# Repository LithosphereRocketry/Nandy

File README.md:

# NANDy
Nandy (capitalization variable) is an 8-bit RISC computer architecture built for implementation using simple 74xx-series discrete NAND gates. It was inspired by the theorem shown in most digital logic classes that any piece of combinational logic may be recreated as a network of NAND gates.

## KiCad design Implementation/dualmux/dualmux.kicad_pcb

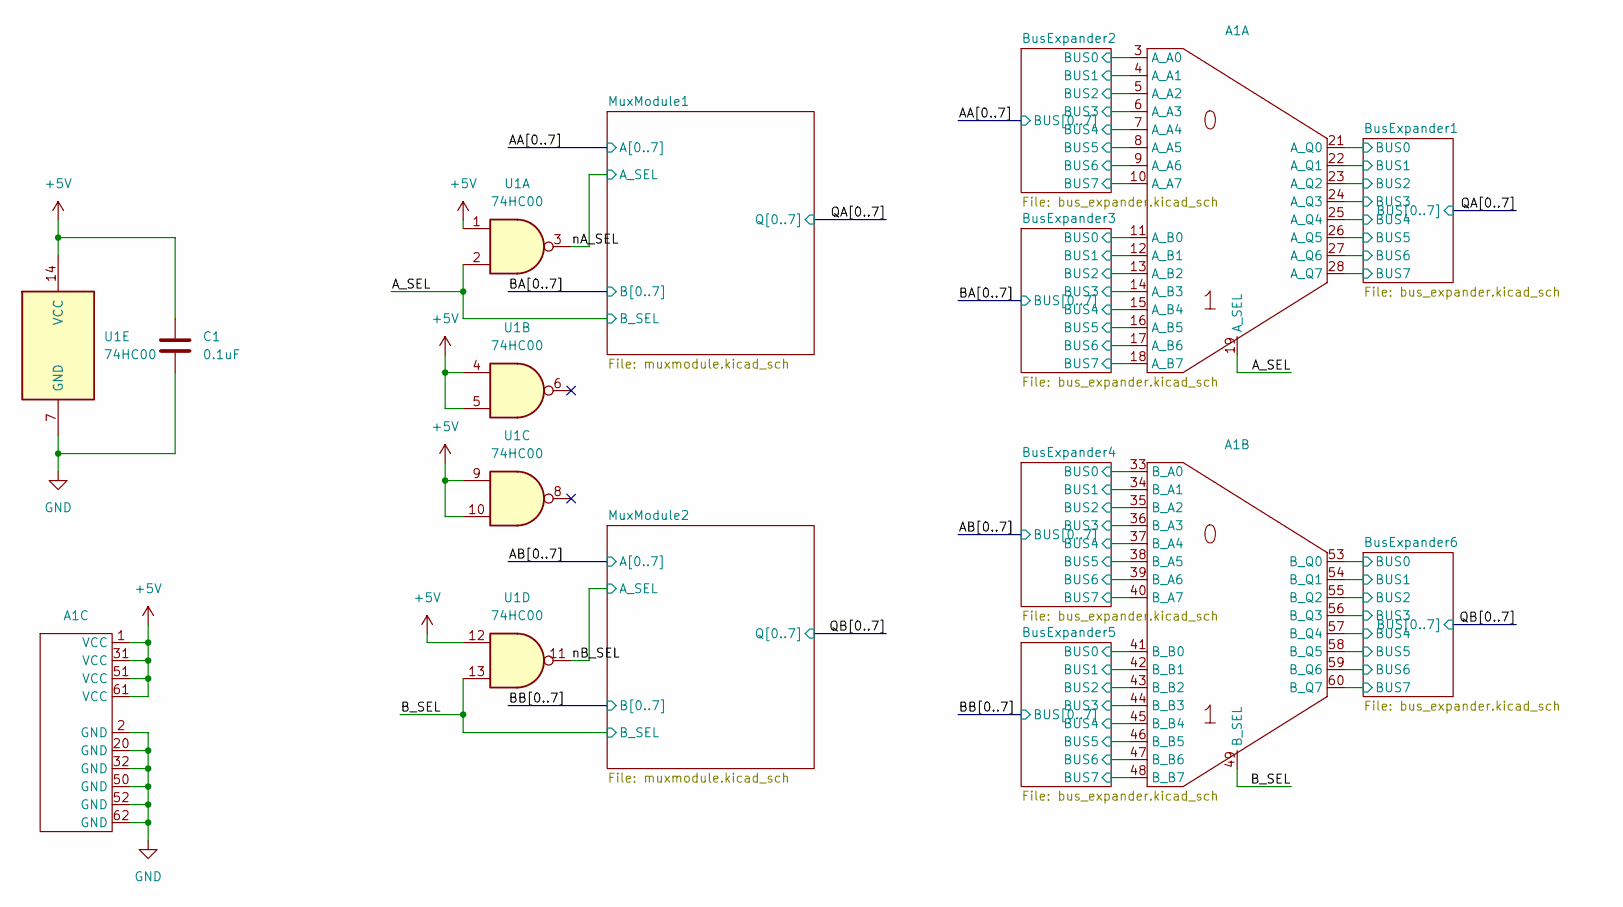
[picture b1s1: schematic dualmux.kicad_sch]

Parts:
A1: EDAC_395-DualMux-CardEdge
C1: 0.1uF; C_Disc_D4.3mm_W1.9mm_P5.00mm
U1: 74HC00; DIP-14_W7.62mm_Socket

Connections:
+5V: A1.1 (VCC), A1.31 (VCC), A1.51 (VCC), A1.61 (VCC), C1.1, U1.1, U1.4, U1.5, U1.9, U1.10, U1.12, U1.14 (VCC); also elsewhere on the board
/AA0: A1.3 (A_A0); also elsewhere on the board
/AA1: A1.4 (A_A1); also elsewhere on the board
/AA2: A1.5 (A_A2); also elsewhere on the board
/AA3: A1.6 (A_A3); also elsewhere on the board
/AA4: A1.7 (A_A4); also elsewhere on the board
/AA5: A1.8 (A_A5); also elsewhere on the board
/AA6: A1.9 (A_A6); also elsewhere on the board
/AA7: A1.10 (A_A7); also elsewhere on the board
/AB0: A1.33 (B_A0); also elsewhere on the board
/AB1: A1.34 (B_A1); also elsewhere on the board
/AB2: A1.35 (B_A2); also elsewhere on the board
/AB3: A1.36 (B_A3); also elsewhere on the board
/AB4: A1.37 (B_A4); also elsewhere on the board
/AB5: A1.38 (B_A5); also elsewhere on the board
/AB6: A1.39 (B_A6); also elsewhere on the board
/AB7: A1.40 (B_A7); also elsewhere on the board
/A_SEL: A1.19 (A_SEL), U1.2; also elsewhere on the board
/BA0: A1.11 (A_B0); also elsewhere on the board
/BA1: A1.12 (A_B1); also elsewhere on the board
/BA2: A1.13 (A_B2); also elsewhere on the board
/BA3: A1.14 (A_B3); also elsewhere on the board
/BA4: A1.15 (A_B4); also elsewhere on the board
/BA5: A1.16 (A_B5); also elsewhere on the board
/BA6: A1.17 (A_B6); also elsewhere on the board
/BA7: A1.18 (A_B7); also elsewhere on the board
/BB0: A1.41 (B_B0); also elsewhere on the board
/BB1: A1.42 (B_B1); also elsewhere on the board
/BB2: A1.43 (B_B2); also elsewhere on the board
/BB3: A1.44 (B_B3); also elsewhere on the board
/BB4: A1.45 (B_B4); also elsewhere on the board
/BB5: A1.46 (B_B5); also elsewhere on the board
/BB6: A1.47 (B_B6); also elsewhere on the board
/BB7: A1.48 (B_B7); also elsewhere on the board
/B_SEL: A1.49 (B_SEL), U1.13; also elsewhere on the board
/QA0: A1.21 (A_Q0); also elsewhere on the board
/QA1: A1.22 (A_Q1); also elsewhere on the board
/QA2: A1.23 (A_Q2); also elsewhere on the board
/QA3: A1.24 (A_Q3); also elsewhere on the board
/QA4: A1.25 (A_Q4); also elsewhere on the board
/QA5: A1.26 (A_Q5); also elsewhere on the board
/QA6: A1.27 (A_Q6); also elsewhere on the board
/QA7: A1.28 (A_Q7); also elsewhere on the board
/QB0: A1.53 (B_Q0); also elsewhere on the board
/QB1: A1.54 (B_Q1); also elsewhere on the board
/QB2: A1.55 (B_Q2); also elsewhere on the board
/QB3: A1.56 (B_Q3); also elsewhere on the board
/QB4: A1.57 (B_Q4); also elsewhere on the board
/QB5: A1.58 (B_Q5); also elsewhere on the board
/QB6: A1.59 (B_Q6); also elsewhere on the board
/QB7: A1.60 (B_Q7); also elsewhere on the board
/nA_SEL: U1.3; also elsewhere on the board
/nB_SEL: U1.11; also elsewhere on the board
GND: A1.2 (GND), A1.20 (GND), A1.32 (GND), A1.50 (GND), A1.52 (GND), A1.62 (GND), C1.2, U1.7 (GND); also elsewhere on the board

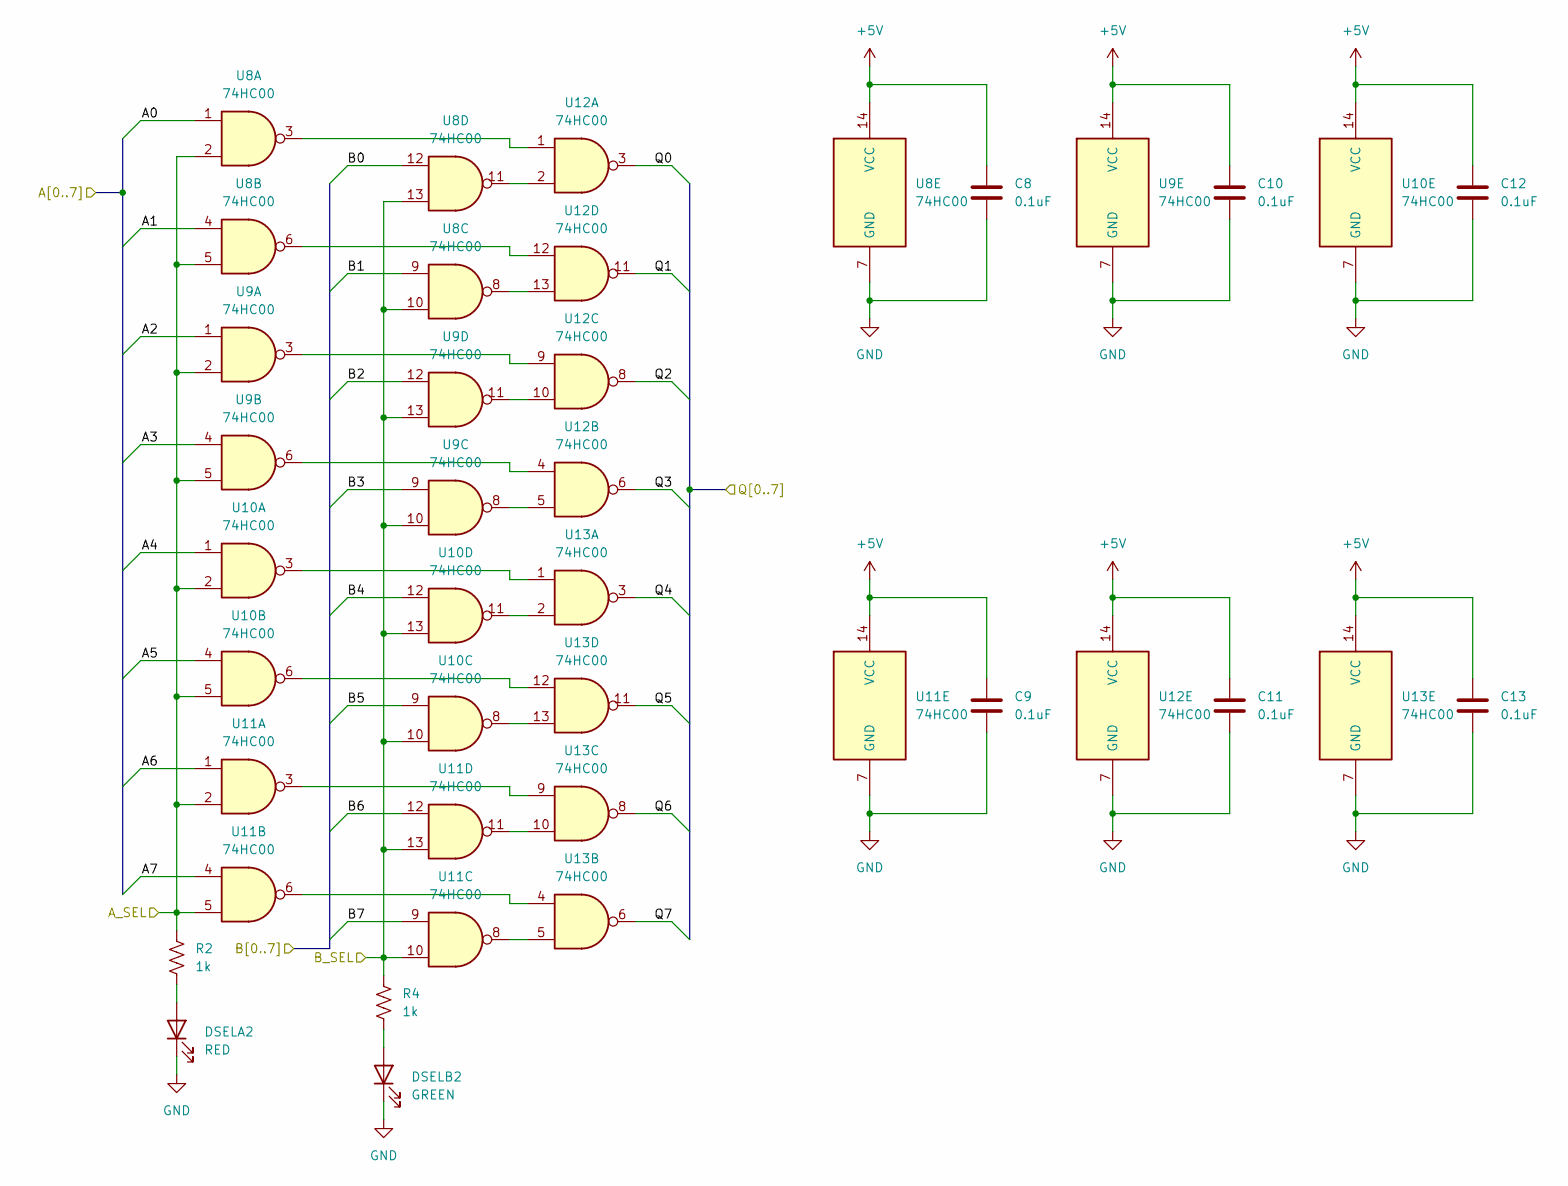
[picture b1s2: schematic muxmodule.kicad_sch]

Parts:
C8, C9, C10, C11, C12, C13: 0.1uF; C_Disc_D4.3mm_W1.9mm_P5.00mm
DSELA2: RED; LED_D5.0mm
DSELB2: GREEN; LED_D5.0mm
R2, R4: 1k; R_Axial_DIN0207_L6.3mm_D2.5mm_P10.16mm_Horizontal
U8, U9, U10, U11, U12, U13: 74HC00; DIP-14_W7.62mm_Socket

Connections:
+5V: C8.1, C9.1, C10.1, C11.1, C12.1, C13.1, U8.14 (VCC), U9.14 (VCC), U10.14 (VCC), U11.14 (VCC), U12.14 (VCC), U13.14 (VCC); also elsewhere on the board
/AB0: U8.1; also elsewhere on the board
/AB1: U8.4; also elsewhere on the board
/AB2: U9.1; also elsewhere on the board
/AB3: U9.4; also elsewhere on the board
/AB4: U10.1; also elsewhere on the board
/AB5: U10.4; also elsewhere on the board
/AB6: U11.1; also elsewhere on the board
/AB7: U11.4; also elsewhere on the board
/BB0: U8.12; also elsewhere on the board
/BB1: U8.9; also elsewhere on the board
/BB2: U9.12; also elsewhere on the board
/BB3: U9.9; also elsewhere on the board
/BB4: U10.12; also elsewhere on the board
/BB5: U10.9; also elsewhere on the board
/BB6: U11.12; also elsewhere on the board
/BB7: U11.9; also elsewhere on the board
/B_SEL: R4.1, U8.10, U8.13, U9.10, U9.13, U10.10, U10.13, U11.10, U11.13; also elsewhere on the board
/QB0: U12.3; also elsewhere on the board
/QB1: U12.11; also elsewhere on the board
/QB2: U12.8; also elsewhere on the board
/QB3: U12.6; also elsewhere on the board
/QB4: U13.3; also elsewhere on the board
/QB5: U13.11; also elsewhere on the board
/QB6: U13.8; also elsewhere on the board
/QB7: U13.6; also elsewhere on the board
/nB_SEL: R2.1, U8.2, U8.5, U9.2, U9.5, U10.2, U10.5, U11.2, U11.5; also elsewhere on the board
GND: C8.2, C9.2, C10.2, C11.2, C12.2, C13.2, DSELA2.1 (K), DSELB2.1 (K), U8.7 (GND), U9.7 (GND), U10.7 (GND), U11.7 (GND), U12.7 (GND), U13.7 (GND); also elsewhere on the board
unnamed: DSELA2.2 (A), R2.2
unnamed: DSELB2.2 (A), R4.2
unnamed: U10.3, U13.1
unnamed: U10.6, U13.12
unnamed: U10.8, U13.13
unnamed: U10.11, U13.2
unnamed: U11.3, U13.9
unnamed: U11.6, U13.4
unnamed: U11.8, U13.5
unnamed: U11.11, U13.10
unnamed: U8.3, U12.1
unnamed: U8.11, U12.2
unnamed: U9.6, U12.4
unnamed: U9.8, U12.5
unnamed: U9.3, U12.9
unnamed: U9.11, U12.10
unnamed: U8.6, U12.12
unnamed: U8.8, U12.13

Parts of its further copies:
C2, C3, C4, C5, C6, C7: 0.1uF; C_Disc_D4.3mm_W1.9mm_P5.00mm
DSELA1: RED; LED_D5.0mm
DSELB1: GREEN; LED_D5.0mm
R1, R3: 1k; R_Axial_DIN0207_L6.3mm_D2.5mm_P10.16mm_Horizontal
U2, U3, U4, U5, U6, U7: 74HC00; DIP-14_W7.62mm_Socket

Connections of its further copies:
+5V: C2.1, C3.1, C4.1, C5.1, C6.1, C7.1, U2.14 (VCC), U3.14 (VCC), U4.14 (VCC), U5.14 (VCC), U6.14 (VCC), U7.14 (VCC); also elsewhere on the board
/AA0: U2.1; also elsewhere on the board
/AA1: U2.4; also elsewhere on the board
/AA2: U3.1; also elsewhere on the board
/AA3: U3.4; also elsewhere on the board
/AA4: U4.1; also elsewhere on the board
/AA5: U4.4; also elsewhere on the board
/AA6: U5.1; also elsewhere on the board
/AA7: U5.4; also elsewhere on the board
/A_SEL: R3.1, U2.10, U2.13, U3.10, U3.13, U4.10, U4.13, U5.10, U5.13; also elsewhere on the board
/BA0: U2.12; also elsewhere on the board
/BA1: U2.9; also elsewhere on the board
/BA2: U3.12; also elsewhere on the board
/BA3: U3.9; also elsewhere on the board
/BA4: U4.12; also elsewhere on the board
/BA5: U4.9; also elsewhere on the board
/BA6: U5.12; also elsewhere on the board
/BA7: U5.9; also elsewhere on the board
/QA0: U6.3; also elsewhere on the board
/QA1: U6.11; also elsewhere on the board
/QA2: U6.8; also elsewhere on the board
/QA3: U6.6; also elsewhere on the board
/QA4: U7.3; also elsewhere on the board
/QA5: U7.11; also elsewhere on the board
/QA6: U7.8; also elsewhere on the board
/QA7: U7.6; also elsewhere on the board
/nA_SEL: R1.1, U2.2, U2.5, U3.2, U3.5, U4.2, U4.5, U5.2, U5.5; also elsewhere on the board
GND: C2.2, C3.2, C4.2, C5.2, C6.2, C7.2, DSELA1.1 (K), DSELB1.1 (K), U2.7 (GND), U3.7 (GND), U4.7 (GND), U5.7 (GND), U6.7 (GND), U7.7 (GND); also elsewhere on the board
unnamed: DSELA1.2 (A), R1.2
unnamed: DSELB1.2 (A), R3.2
unnamed: U2.3, U6.1
unnamed: U2.6, U6.12
unnamed: U2.8, U6.13
unnamed: U2.11, U6.2
unnamed: U3.3, U6.9
unnamed: U3.6, U6.4
unnamed: U3.8, U6.5
unnamed: U3.11, U6.10
unnamed: U4.3, U7.1
unnamed: U4.6, U7.12
unnamed: U4.8, U7.13
unnamed: U4.11, U7.2
unnamed: U5.3, U7.9
unnamed: U5.6, U7.4
unnamed: U5.8, U7.5
unnamed: U5.11, U7.10

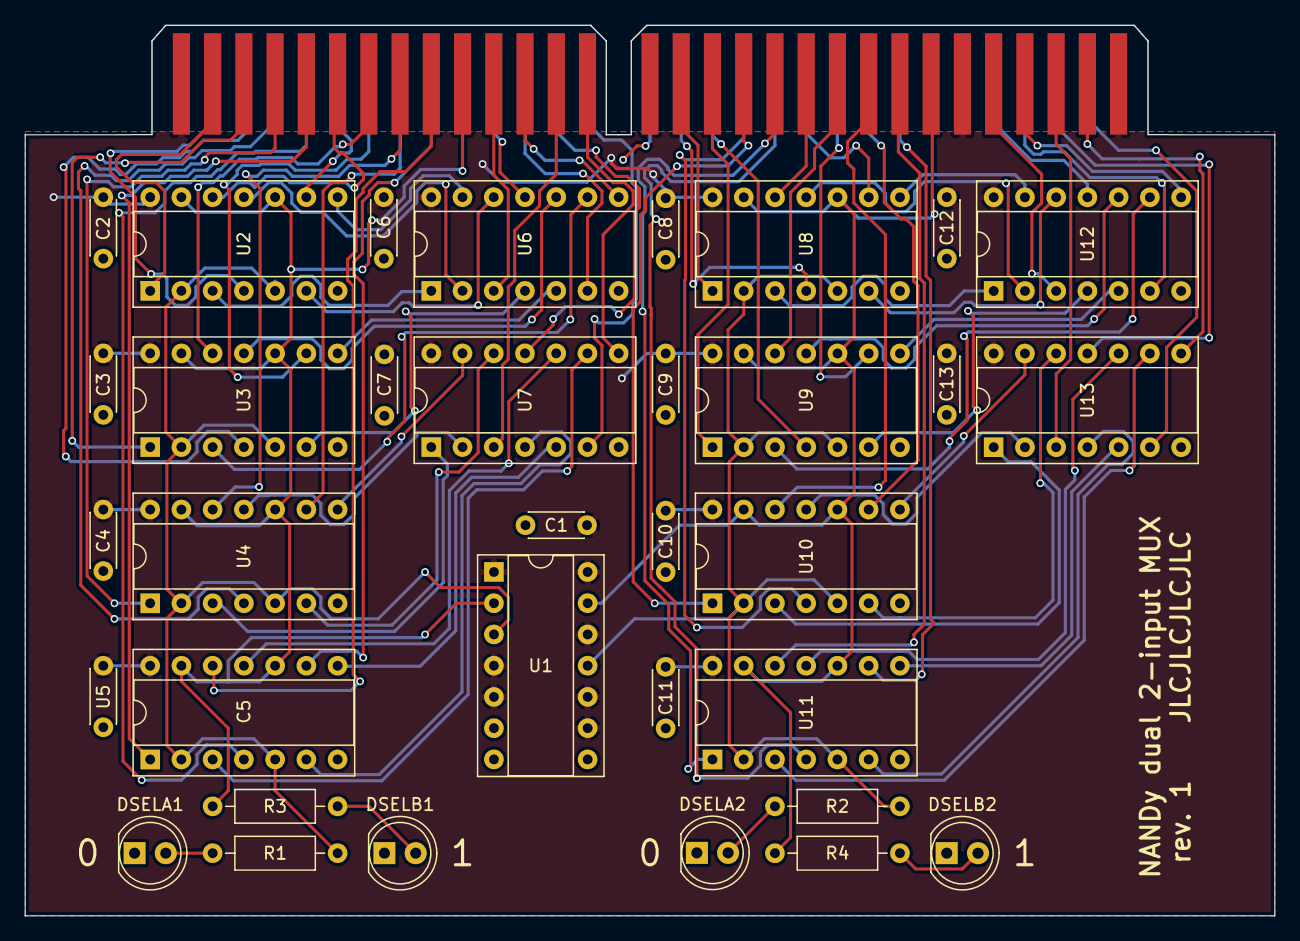
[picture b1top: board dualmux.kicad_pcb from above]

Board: 2 copper layers, 101.6 x 72.4 mm, 35 parts (1 on the bottom side), 90 nets.

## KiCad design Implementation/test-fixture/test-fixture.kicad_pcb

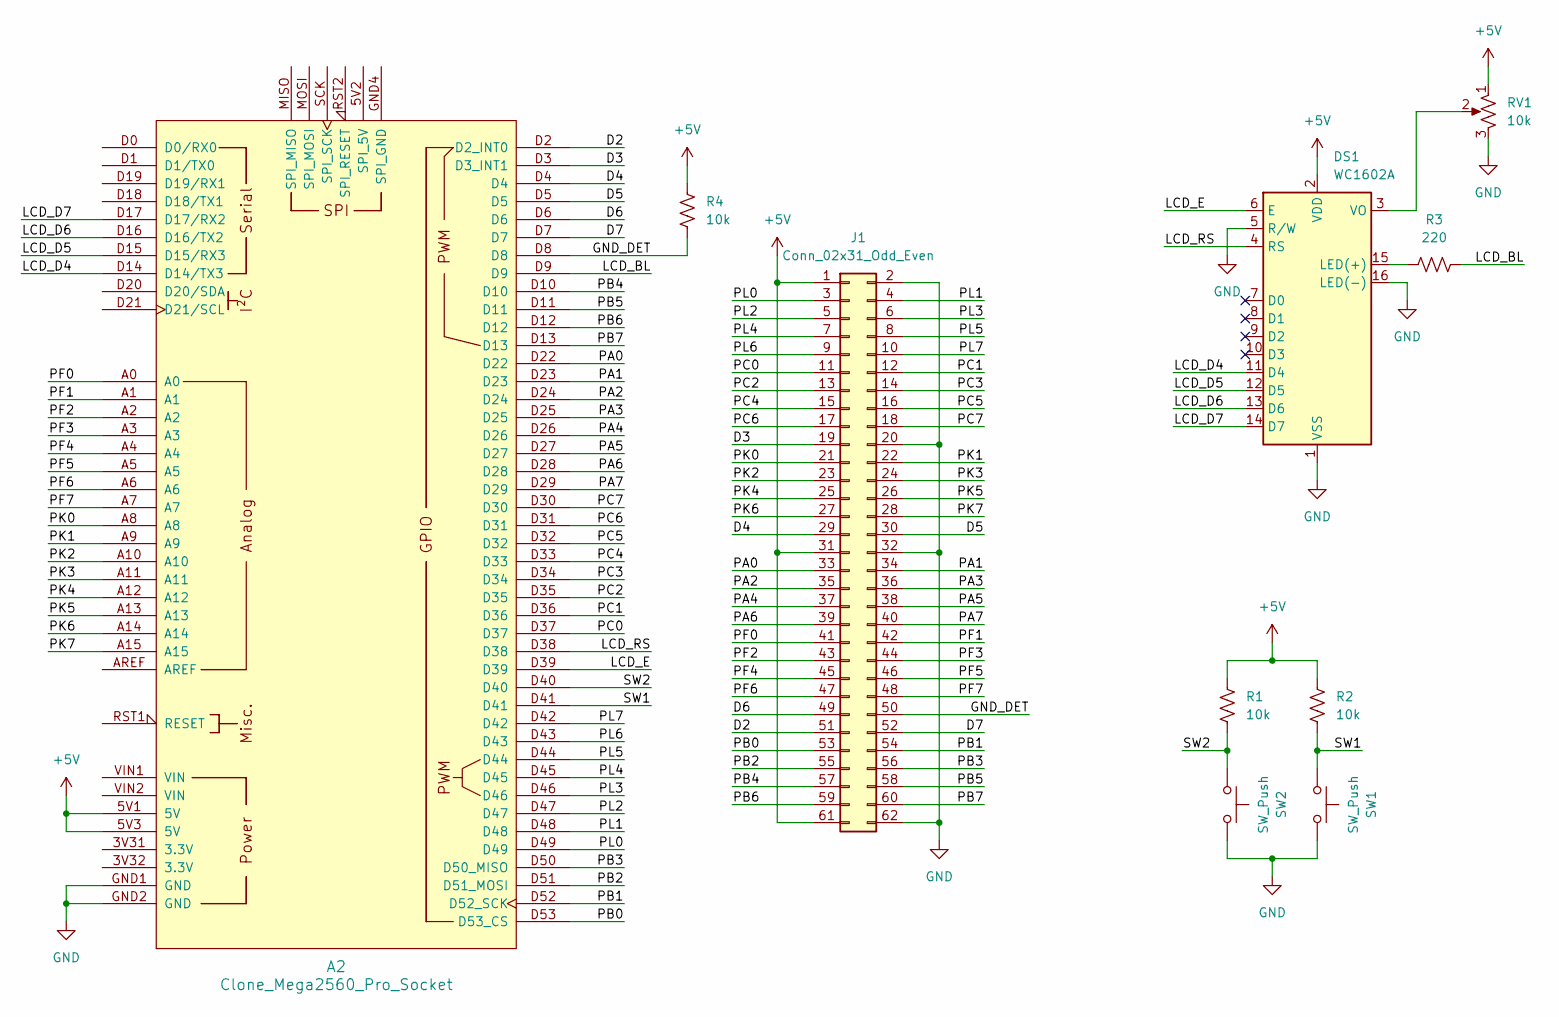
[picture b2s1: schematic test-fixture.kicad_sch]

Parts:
A2: Clone_Mega2560_Pro_Socket
DS1: WC1602A
J1: Conn_02x31_Odd_Even; EDAC_395-062-520-350
R1, R2, R4: 10k; R_Axial_DIN0207_L6.3mm_D2.5mm_P10.16mm_Horizontal
R3: 220; R_Axial_DIN0207_L6.3mm_D2.5mm_P10.16mm_Horizontal
RV1: 10k; Potentiometer_ACP_CA9-V10_Vertical
SW1, SW2: SW_Push; SW_PUSH_6mm

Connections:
+5V: A2.5V1 (5V), A2.5V3 (5V), DS1.2 (VDD), J1.1, J1.31, J1.61, R1.1, R2.1, R4.1, RV1.1
/D2: A2.D2 (D2_INT0), J1.51
/D3: A2.D3 (D3_INT1), J1.19
/D4: A2.D4, J1.29
/D5: A2.D5, J1.30
/D6: A2.D6, J1.49
/D7: A2.D7, J1.52
/GND_DET: A2.D8, J1.50, R4.2
/LCD_BL: A2.D9, R3.2
/LCD_D4: A2.D14 (D14/TX3), DS1.11 (D4)
/LCD_D5: A2.D15 (D15/RX3), DS1.12 (D5)
/LCD_D6: A2.D16 (D16/TX2), DS1.13 (D6)
/LCD_D7: A2.D17 (D17/RX2), DS1.14 (D7)
/LCD_E: A2.D39, DS1.6 (E)
/LCD_RS: A2.D38, DS1.4 (RS)
/PA0: A2.D22, J1.33
/PA1: A2.D23, J1.34
/PA2: A2.D24, J1.35
/PA3: A2.D25, J1.36
/PA4: A2.D26, J1.37
/PA5: A2.D27, J1.38
/PA6: A2.D28, J1.39
/PA7: A2.D29, J1.40
/PB0: A2.D53 (D53_CS), J1.53
/PB1: A2.D52 (D52_SCK), J1.54
/PB2: A2.D51 (D51_MOSI), J1.55
/PB3: A2.D50 (D50_MISO), J1.56
/PB4: A2.D10, J1.57
/PB5: A2.D11, J1.58
/PB6: A2.D12, J1.59
/PB7: A2.D13, J1.60
/PC0: A2.D37, J1.11
/PC1: A2.D36, J1.12
/PC2: A2.D35, J1.13
/PC3: A2.D34, J1.14
/PC4: A2.D33, J1.15
/PC5: A2.D32, J1.16
/PC6: A2.D31, J1.17
/PC7: A2.D30, J1.18
/PF0: A2.A0, J1.41
/PF1: A2.A1, J1.42
/PF2: A2.A2, J1.43
/PF3: A2.A3, J1.44
/PF4: A2.A4, J1.45
/PF5: A2.A5, J1.46
/PF6: A2.A6, J1.47
/PF7: A2.A7, J1.48
/PK0: A2.A8, J1.21
/PK1: A2.A9, J1.22
/PK2: A2.A10, J1.23
/PK3: A2.A11, J1.24
/PK4: A2.A12, J1.25
/PK5: A2.A13, J1.26
/PK6: A2.A14, J1.27
/PK7: A2.A15, J1.28
/PL0: A2.D49, J1.3
/PL1: A2.D48, J1.4
/PL2: A2.D47, J1.5
/PL3: A2.D46, J1.6
/PL4: A2.D45, J1.7
/PL5: A2.D44, J1.8
/PL6: A2.D43, J1.9
/PL7: A2.D42, J1.10
/SW1: A2.D41, R2.2, SW1.1
/SW2: A2.D40, R1.2, SW2.1
GND: A2.GND1 (GND), A2.GND2 (GND), DS1.1 (VSS), DS1.5 (R/W), DS1.16 (LED(-)), J1.2, J1.20, J1.32, J1.62, RV1.3, SW1.2, SW2.2
unnamed: DS1.15 (LED(+)), R3.1
unnamed: DS1.3 (VO), RV1.2

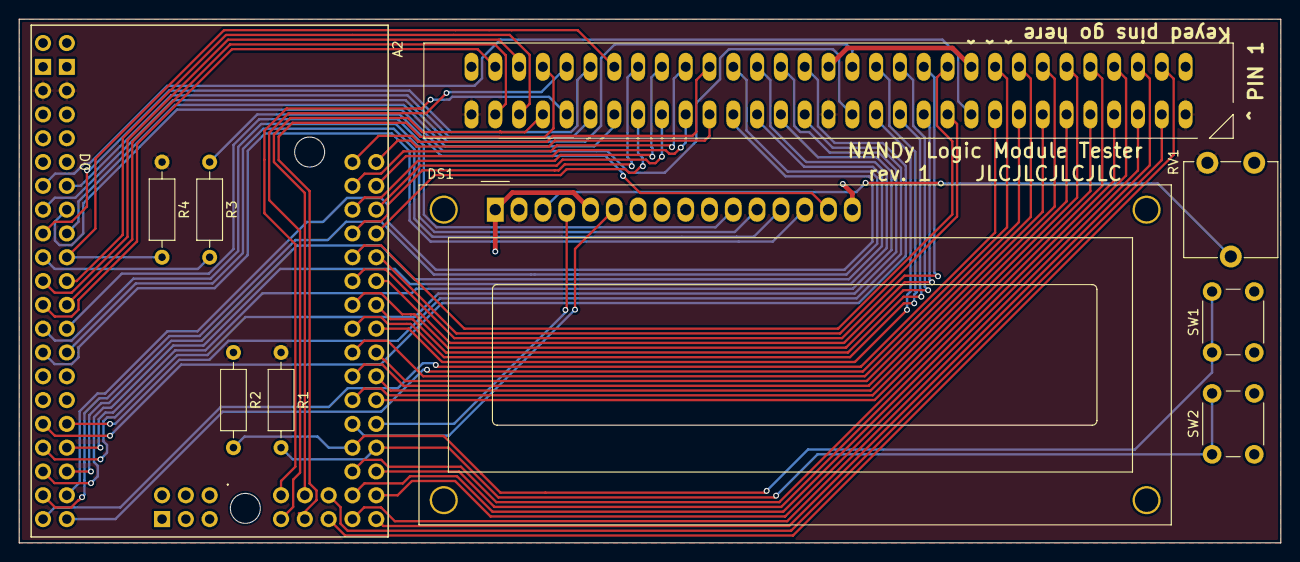
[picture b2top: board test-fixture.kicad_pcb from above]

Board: 2 copper layers, 134.6 x 55.9 mm, 10 parts (0 on the bottom side), 68 nets.

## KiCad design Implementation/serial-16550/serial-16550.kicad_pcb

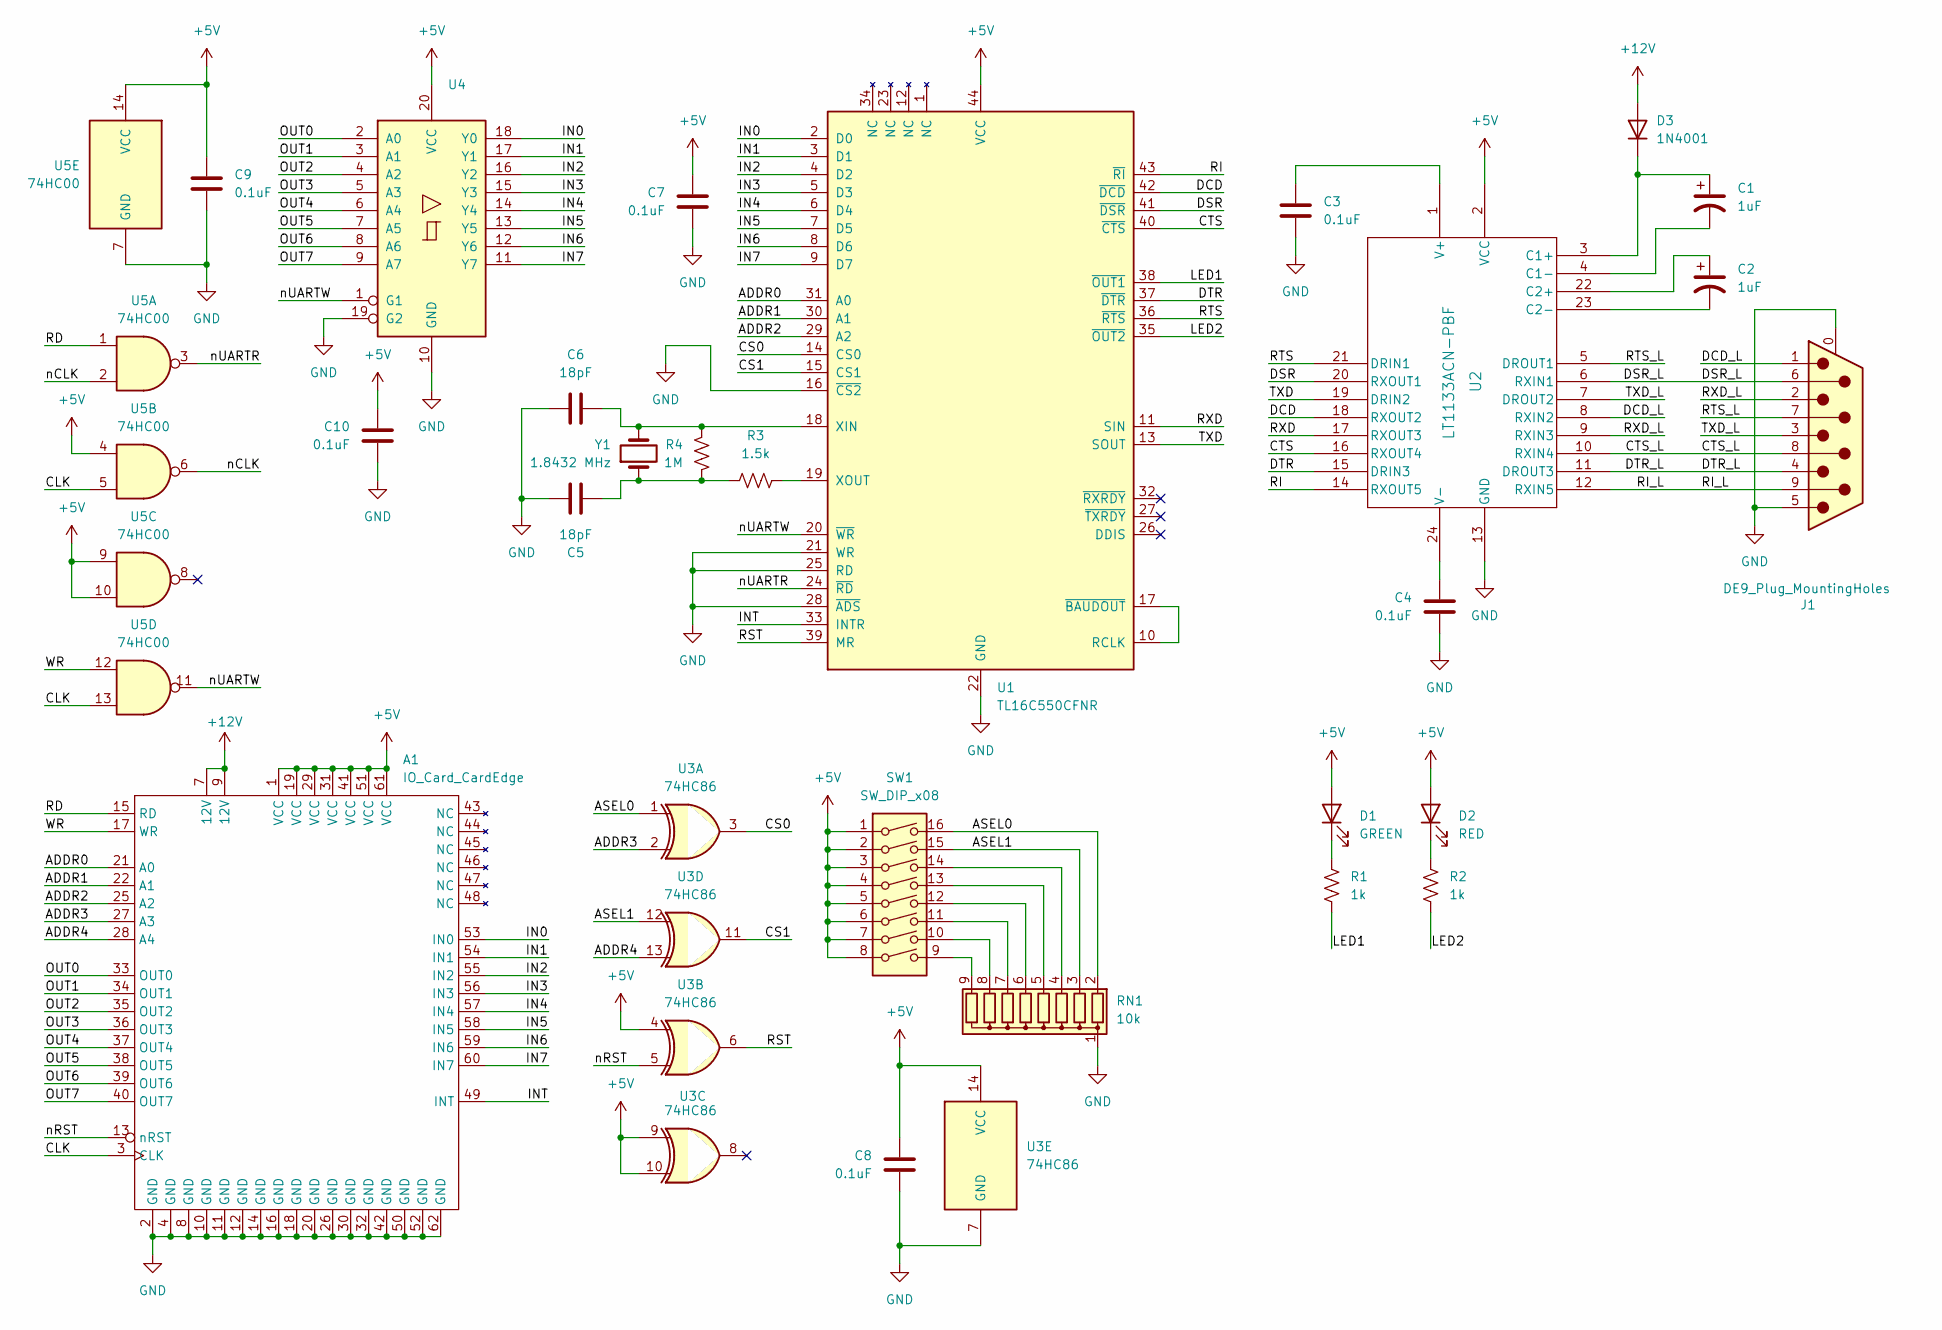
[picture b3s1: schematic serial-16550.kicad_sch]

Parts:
A1: IO_Card_CardEdge; EDAC_395-062-IOCard-CardEdge
C1, C2: 1uF; CP_Radial_Tantal_D7.0mm_P5.00mm
C3, C4, C7, C8, C9, C10: 0.1uF; C_Disc_D4.3mm_W1.9mm_P5.00mm
C5, C6: 18pF; C_Disc_D4.3mm_W1.9mm_P5.00mm
D1: GREEN; LED_D5.0mm
D2: RED; LED_D5.0mm
D3: 1N4001; D_DO-41_SOD81_P10.16mm_Horizontal
J1: DE9_Plug_MountingHoles; DSUB-9_Male_Horizontal_P2.77x2.84mm_EdgePinOffset7.70mm_Hou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
R1, R2: 1k; R_Axial_DIN0207_L6.3mm_D2.5mm_P10.16mm_Horizontal
R3: 1.5k; R_Axial_DIN0207_L6.3mm_D2.5mm_P10.16mm_Horizontal
R4: 1M; R_Axial_DIN0207_L6.3mm_D2.5mm_P10.16mm_Horizontal
RN1: 10k; R_Array_SIP9
SW1: SW_DIP_x08; SW_DIP_SPSTx08_Slide_6.7x21.88mm_W7.62mm_P2.54mm_LowProfile
U1: TL16C550CFNR; PLCC-44_THT-Socket
U2: LT1133ACN-PBF; DIP-24_W7.62mm
U3: 74HC86; DIP-14_W7.62mm_Socket
U4: 74AHC541; DIP-20_W7.62mm_Socket
U5: 74HC00; DIP-14_W7.62mm_Socket
Y1: 1.8432 MHz; Crystal_HC49-U_Vertical

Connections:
+5V: A1.1 (VCC), A1.19 (VCC), A1.29 (VCC), A1.31 (VCC), A1.41 (VCC), A1.51 (VCC), A1.61 (VCC), C7.1, C8.1, C9.1, C10.1, D1.2 (A), D2.2 (A), SW1.1, SW1.2, SW1.3, SW1.4, SW1.5, SW1.6, SW1.7, SW1.8, U1.44 (VCC), U2.2 (VCC), U3.4, U3.9, U3.10, U3.14 (VCC), U4.20 (VCC), U5.4, U5.9, U5.10, U5.14 (VCC)
+12V: A1.7 (12V), A1.9 (12V), D3.2 (A)
/ADDR0: A1.21 (A0), U1.31 (A0)
/ADDR1: A1.22 (A1), U1.30 (A1)
/ADDR2: A1.25 (A2), U1.29 (A2)
/ADDR3: A1.27 (A3), U3.2
/ADDR4: A1.28 (A4), U3.13
/ASEL0: RN1.2 (R1), SW1.16, U3.1
/ASEL1: RN1.3 (R2), SW1.15, U3.12
/CLK: A1.3 (CLK), U5.5, U5.13
/CS0: U1.14 (CS0), U3.3
/CS1: U1.15 (CS1), U3.11
/CTS: U1.40 (~CTS), U2.16 (RXOUT4)
/CTS_L: J1.8, U2.10 (RXIN4)
/DCD: U1.42 (~DCD), U2.18 (RXOUT2)
/DCD_L: J1.1, U2.8 (RXIN2)
/DSR: U1.41 (~DSR), U2.20 (RXOUT1)
/DSR_L: J1.6, U2.6 (RXIN1)
/DTR: U1.37 (~DTR), U2.15 (DRIN3)
/DTR_L: J1.4, U2.11 (DROUT3)
/IN0: A1.53 (IN0), U1.2 (D0), U4.18 (Y0)
/IN1: A1.54 (IN1), U1.3 (D1), U4.17 (Y1)
/IN2: A1.55 (IN2), U1.4 (D2), U4.16 (Y2)
/IN3: A1.56 (IN3), U1.5 (D3), U4.15 (Y3)
/IN4: A1.57 (IN4), U1.6 (D4), U4.14 (Y4)
/IN5: A1.58 (IN5), U1.7 (D5), U4.13 (Y5)
/IN6: A1.59 (IN6), U1.8 (D6), U4.12 (Y6)
/IN7: A1.60 (IN7), U1.9 (D7), U4.11 (Y7)
/INT: A1.49 (INT), U1.33 (INTR)
/LED1: R1.2, U1.38 (~OUT1)
/LED2: R2.2, U1.35 (~OUT2)
/OUT0: A1.33 (OUT0), U4.2 (A0)
/OUT1: A1.34 (OUT1), U4.3 (A1)
/OUT2: A1.35 (OUT2), U4.4 (A2)
/OUT3: A1.36 (OUT3), U4.5 (A3)
/OUT4: A1.37 (OUT4), U4.6 (A4)
/OUT5: A1.38 (OUT5), U4.7 (A5)
/OUT6: A1.39 (OUT6), U4.8 (A6)
/OUT7: A1.40 (OUT7), U4.9 (A7)
/RD: A1.15 (RD), U5.1
/RI: U1.43 (~RI), U2.14 (RXOUT5)
/RI_L: J1.9, U2.12 (RXIN5)
/RST: U1.39 (MR), U3.6
/RTS: U1.36 (~RTS), U2.21 (DRIN1)
/RTS_L: J1.7, U2.5 (DROUT1)
/RXD: U1.11 (SIN), U2.17 (RXOUT3)
/RXD_L: J1.2, U2.9 (RXIN3)
/TXD: U1.13 (SOUT), U2.19 (DRIN2)
/TXD_L: J1.3, U2.7 (DROUT2)
/WR: A1.17 (WR), U5.12
/nCLK: U5.2, U5.6
/nRST: A1.13 (nRST), U3.5
/nUARTR: U1.24 (~RD), U5.3
/nUARTW: U1.20 (~WR), U4.1 (G1), U5.11
GND: A1.2 (GND), A1.4 (GND), A1.8 (GND), A1.10 (GND), A1.11 (GND), A1.12 (GND), A1.14 (GND), A1.16 (GND), A1.18 (GND), A1.20 (GND), A1.26 (GND), A1.30 (GND), A1.32 (GND), A1.42 (GND), A1.50 (GND), A1.52 (GND), A1.62 (GND), C3.2, C4.2, C5.1, C6.2, C7.2, C8.2, C9.2, C10.2, J1.0 (PAD), J1.5, RN1.1 (common), U1.16 (~CS2), U1.21 (WR), U1.22 (GND), U1.25 (RD), U1.28 (~ADS), U2.13 (GND), U3.7 (GND), U4.10 (GND), U4.19 (G2), U5.7 (GND)
unnamed: C5.2, R3.1, R4.2, Y1.1
unnamed: D1.1 (K), R1.1
unnamed: D2.1 (K), R2.1
unnamed: C1.1, D3.1 (K), U2.3 (C1+)
unnamed: RN1.4 (R3), SW1.14
unnamed: RN1.5 (R4), SW1.13
unnamed: RN1.6 (R5), SW1.12
unnamed: RN1.7 (R6), SW1.11
unnamed: RN1.8 (R7), SW1.10
unnamed: RN1.9 (R8), SW1.9
unnamed: U1.10 (RCLK), U1.17 (~BAUDOUT)
unnamed: C6.1, R4.1, U1.18 (XIN), Y1.2
unnamed: R3.2, U1.19 (XOUT)
unnamed: C1.2, U2.4 (C1-)
unnamed: C2.1, U2.22 (C2+)
unnamed: C2.2, U2.23 (C2-)
unnamed: C3.1, U2.1 (V+)
unnamed: C4.1, U2.24 (V-)

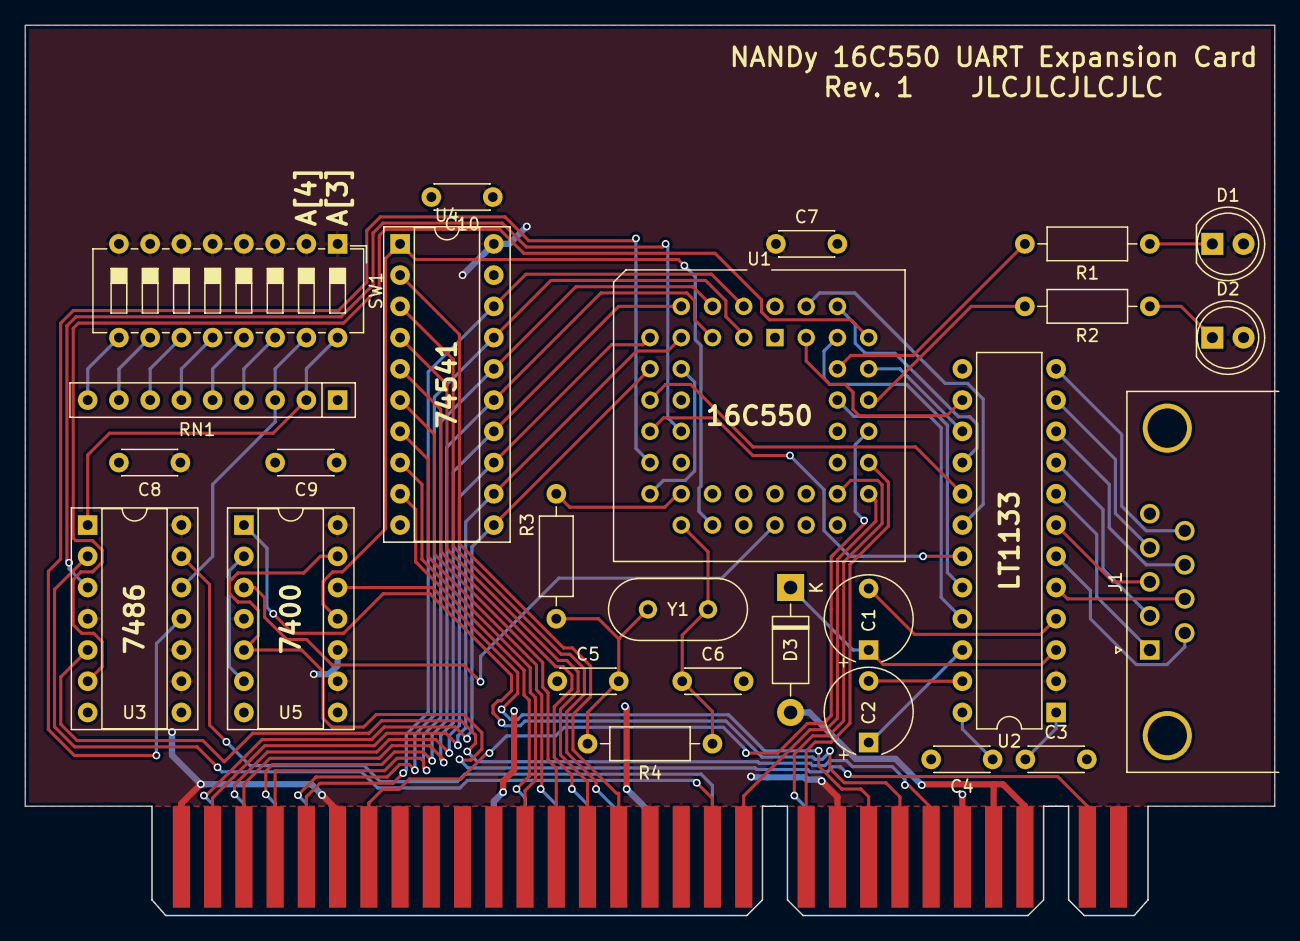
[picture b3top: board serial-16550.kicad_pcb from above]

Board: 2 copper layers, 101.6 x 72.4 mm, 27 parts (1 on the bottom side), 73 nets.
